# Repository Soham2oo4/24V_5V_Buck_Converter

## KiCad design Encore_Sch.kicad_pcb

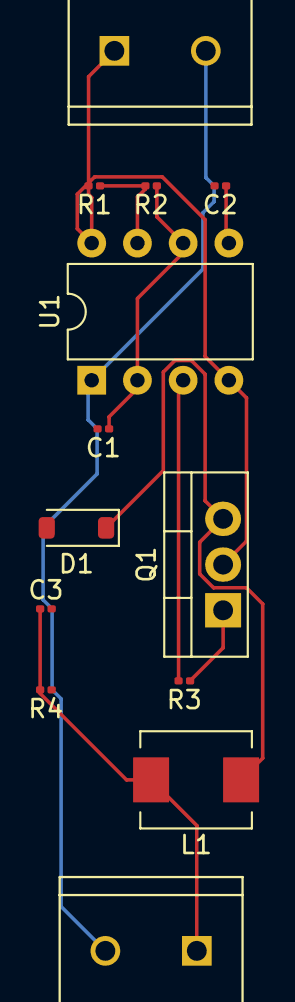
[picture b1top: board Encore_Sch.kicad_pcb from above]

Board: 2 copper layers, 13 parts (0 on the bottom side), 9 nets.

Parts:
C1: 100pf; C_0201_0603Metric
C2: 0.01u; C_0201_0603Metric
C3: 11.64u; C_0201_0603Metric
D1: MBR0540; D_SOD-123
L1: 11.35u; L_Neosid_SM-PIC0512H
P1, P2: 282837-2; TE_282837-2
Q1: IRLZ44N; TO-220-3_Vertical
R1: 28k; R_0201_0603Metric
R2: 10k; R_0201_0603Metric
R3: 470; R_0201_0603Metric
R4: 1.073; R_0201_0603Metric
U1: ICM7555xP; DIP-8_W7.62mm

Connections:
GND: C1.2, C2.2, C3.2, D1.2 (A), P1.2, P2.2, R4.1, U1.1 (GND)
unnamed: C3.1, L1.2, P1.1, R4.2
unnamed: D1.1 (K), L1.1, Q1.3 (S)
unnamed: P2.1, Q1.2 (D), R1.2, U1.4 (R), U1.8 (VCC)
unnamed: Q1.1 (G), R3.1
unnamed: C2.1, U1.5 (CV)
unnamed: R1.1, R2.2, U1.7 (DIS)
unnamed: R3.2, U1.3 (Q)
unnamed: C1.1, R2.1, U1.2 (TR), U1.6 (THR)

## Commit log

2024-09-26 Bill of Materials
2024-09-26 KiCad Files (Schematic and PCB)
2024-09-26 PCB_file
2024-09-26 Project file
2024-09-26 Schematic of PCB
2024-09-26 document
2024-09-26 Create test
2024-09-26 datasheets
2024-10-09 Rename En_Core_Team13.docx to 5V_24V_buck.docx
2024-10-09 Rename Encore_Sch.kicad_pro to 5V_24V_buck.kicad_pro
2024-10-09 Rename BOM_Encore.docx to Bill_of_Material.docx
